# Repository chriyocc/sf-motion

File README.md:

# SF-Motion

**Open-source BLDC/PMSM motor control platform based on STM32 and Field-Oriented Control (FOC).**

The project includes:

- FOC firmware
- Custom motor driver hardware
- KiCad schematic and PCB design
- Gerber and BOM files
- Python communication and control tools
- PyQt/PyQtGraph GUI for motor monitoring and testing

> ⚠️ This project is under active development. Hardware and firmware may change between versions.

## My Tips
For everyday operation, calibration, control modes, plotting, and troubleshooting, see the [complete motor user guide](MOTOR_USER_GUIDE.md).

To start virtual env
`Set-ExecutionPolicy -Scope Process -ExecutionPolicy Bypass`
`.venv\Scripts\Activate.ps1`

To start GUI
`python communication/motor.py`

## Hardware Prerequisites

You will need:
- FOC Driver Board
- ST-Link programmer/debugger with 3-pin Molex pico-blade P1.25mm connector
- DC power supply
- BLDC/PMSM motor
- diametrical magnet
- USB type-C cable
- power cable with XT-30 female connector

The hardware design is available in:
```
Hardware/
├── production/        # Gerber manufacturing files
├── .kicad_sch         # Schematic
├── .kicad_pcb         # PCB design
└── ...
```

## Software Prerequisites

### 1. STM32CubeMX

Used to configure the STM32 peripherals and generate the initial project configuration.

Download: https://www.st.com/en/development-tools/stm32cubemx.html

### 2. Visual Studio Code

Used as the main development environment.

Download: https://code.visualstudio.com/

### 3. PlatformIO

PlatformIO is used to build and upload the firmware.

Install PlatformIO through the VS Code extension:
1. Open VS Code.
2. Open Extensions.
3. Search for PlatformIO IDE.
4. Install the extension.
5. Restart VS Code if required.

Verify the installation:
``` bash
pio --version
```

If `pio` is not recognized in the terminal, use the PlatformIO terminal inside VS Code or add the PlatformIO CLI directory to your system PATH.

### 4. Python

Python is required for the communication tools and GUI.

Recommended version:
```text
Python 3.10+
```

Download: https://www.python.org/downloads/

Check the installation:
``` bash
python --version
```

Create a virtual environment (recommended):
``` bash
python -m venv .venv
```

Activate it on Windows:
``` bash
.venv\Scripts\activate
```

Activate it on Linux/macOS:
``` bash
source .venv/bin/activate
```

Install the required packages:
``` bash
pip install numpy pyserial PyQt5 pyqtgraph keyboard
```

## Getting Started

Clone the repository using Git:
``` bash
git clone https://github.com/sirojudinMunir/sf-motion.git
```

Enter the project directory:
``` bash
cd SF-Motion
```

## Building the Firmware

Open the project in VS Code with PlatformIO installed.

Build the firmware:
``` bash
pio run
```

If the build is successful, the firmware binary will be generated by PlatformIO.

## Upload Firmware

Connect the ST-Link to the FOC Driver board using the 3-pin PicoBlade connector.

The board can be powered from a **6–24 V external power supply**. For the initial test, it is recommended to use **USB Type-C** as the power source if applicable.

Upload the firmware:
``` bash
pio run -t upload
```

You can also use the Upload button in the PlatformIO interface in VS Code.

## For the first test

After uploading the firmware, follow these steps:

1. Make sure the D3 LED is blinking after the firmware starts.
2. Connect the BLDC/PMSM motor wires to the FOC Driver board. Make sure the diametrical magnet is securely mounted on the motor shaft and properly aligned with the magnetic encoder on the FOC Driver board. The board should be positioned directly beneath the magnet.
3. If you are using an external power supply, set the current limit to 1 A for the initial test. This helps prevent damage if there is an unexpected issue with the board or motor.
4. Connect the USB Type-C cable to the board.
5. Run the Python motor control program:
    ```python
    python communication/motor.py
    ```
6. Select the correct COM port and click Connect.

7. Before running the motor, set the correct motor pole pairs:
    ``` python
    motor.set_pole_pairs(<your_motor_pole_pairs>)
    ```
    Replace <your_motor_pole_pairs> with the actual number of pole pairs of your motor.
8. Run the self-commissioning process:
    ``` python
    motor.self_commissioning()
    ```
    The self-commissioning process measures the motor resistance and inductance and calibrates the magnetic encoder.
    >Important: During encoder calibration, make sure the motor rotates counter-clockwise (CCW). If the motor rotates in the opposite direction, swap any two motor wires to reverse the rotation.
    Automatic motor direction detection will be implemented in a future version.
9. Save configuration
    ``` python
    motor.set_save_config()
    ```
10. Test the FOC motor modes using:
    ``` python
    motor.set_motor_mode(<mode>)
    ```
    Available modes:

    0 -> for current control mode  
    1 -> for speed control mode  
    2 -> for position control mode  
    5 -> for open-loop mode  
    6 -> for disable the motor

> ⚠️ Keep the power supply current limit low during the first test. Do not increase the voltage or current limit until the board, encoder, and motor are confirmed to be working correctly.

---

## Support SF-Motion

If you find this project useful and would like to support its development,
you can become a sponsor:

Your support helps fund hardware development, testing, documentation,
and future improvements to SF-Motion.

## Update Needed
- Implement overcurrent protection (send fault through CAN)
- 

## Updates compared with the earlier version (2026-09-23)

This section records the firmware, custom GUI, and communication fixes made after the PID/control review. The comparison is against the code before those fixes, rather than a tagged release.

### Firmware changes

| Area | Earlier behavior | Updated behavior |
| --- | --- | --- |
| Saved position PID cutoff | Startup replaced the saved derivative filter cutoff with 20 Hz. | Startup preserves the saved cutoff and recalculates its coefficient after setting the sampling period. |
| PI/PID anti-windup | The integral could keep growing when the proportional term, or combined P+D term, already exceeded the output limit. | Integration stops when it would drive the output further into saturation, while allowing the integral to unwind. |
| PID validation and acknowledgements | Negative gains could be ignored while returning success; negative output maxima could invert the bounds. | PID setters reject invalid values and return an error through the communication protocol. Validation includes non-finite values, ordered output bounds, nonnegative gains/deadbands, and positive filter cutoff and sampling period. |
| PID reset | Reset cleared the integral and previous error but retained filtered derivative history. | Reset also clears the filtered derivative history. |
| USB transmit buffer | A new frame could overwrite bytes still being used by an outstanding USB transfer. | CDC checks availability, then copies the frame into its own transmit buffer before starting the transfer. Oversized frames are rejected. |

### Custom GUI and Python communication changes

These control changes apply to `communication/plotter_custom.py`; the shared protocol changes are in `communication/SFMotionCom.py` and `communication/MotorProtocol.py`.

| Area | Earlier behavior | Updated behavior |
| --- | --- | --- |
| Disable command | A timeout while sending a zero current/speed setpoint could prevent the disable command from being sent. | The GUI attempts disable even when the preliminary zero fails. An unconfirmed disable is reported as unconfirmed. |
| Relative position moves | Targets used the last plotted angle, which became stale when plotting was paused. | The GUI reads the angle directly from the board before calculating a relative target. A failed or non-finite read cancels the move. The position demo also reads its starting angle directly. |
| Reconnect and Apply All | Previously loaded parameters remained eligible for Apply All after reconnecting. | Reconnect, disconnect, a failed Read All, or a failed Apply All invalidates the loaded-parameter state. A successful Read All is required before Apply All is allowed again. |
| PID input fields | PID fields allowed negative values regardless of their meaning. | Gains, deadbands, and output maxima are nonnegative; derivative cutoff is positive; field-weakening output minimum is nonpositive. The protocol validates all values in a PID group before its first write. |
| Request/reply handling | Requests consumed the next queued reply, allowing delayed replies to disrupt later requests. | Requests are serialized. A timeout, transport failure, or malformed/mismatched reply invalidates the session and requires reconnecting. A disable write remains possible, but is explicitly unconfirmed in that state. |
| Partial parameter updates | Failure during a group write could leave some registers updated without a clear recovery instruction. | Failures explicitly report a possible partial update and instruct the user to reconnect if required, then read parameters before retrying. |
| Connection setup failures | Only serial-specific exceptions were caught during connection setup. | Setup failures also clean up the connection and report the error. |

### Applying the update

- **Firmware changes require a successful flash and verification.** Building alone does not update the board.
- Build the main firmware with `pio run -e genericSTM32F405RG`. The output is `.pio/build/genericSTM32F405RG/firmware.bin`.
- **GUI changes require restarting the Python GUI.** After connecting, use Read All Parameters before Apply All.
- PID register mappings and the on-wire frame format remain unchanged.

### Validation and remaining limitations

- The main firmware build passed.
- All 16 Python GUI/protocol tests passed, including the two existing plotting tests and 14 new regression tests. Serial interactions in these tests are mocked.
- Added C regression tests for PI/PID saturation and unwinding, invalid values, filter initialization, and reset behavior. They were compiled with the ARM toolchain but have not been executed here.
- PID groups still use separate register writes; they are **not atomic**. A connection failure can leave a partial update, and automatic rollback is not attempted.
- Motor behavior and USB transfer behavior have not been verified on hardware. The reported CubeProgrammer erase failure remains unresolved; the updated firmware has not been confirmed installed on the board.
- The VCAP capacitor values discussed during troubleshooting are a hardware check, not a hardware modification included in this update.

See [hardware-free test instructions and communication recovery](tests/README.md) for details.

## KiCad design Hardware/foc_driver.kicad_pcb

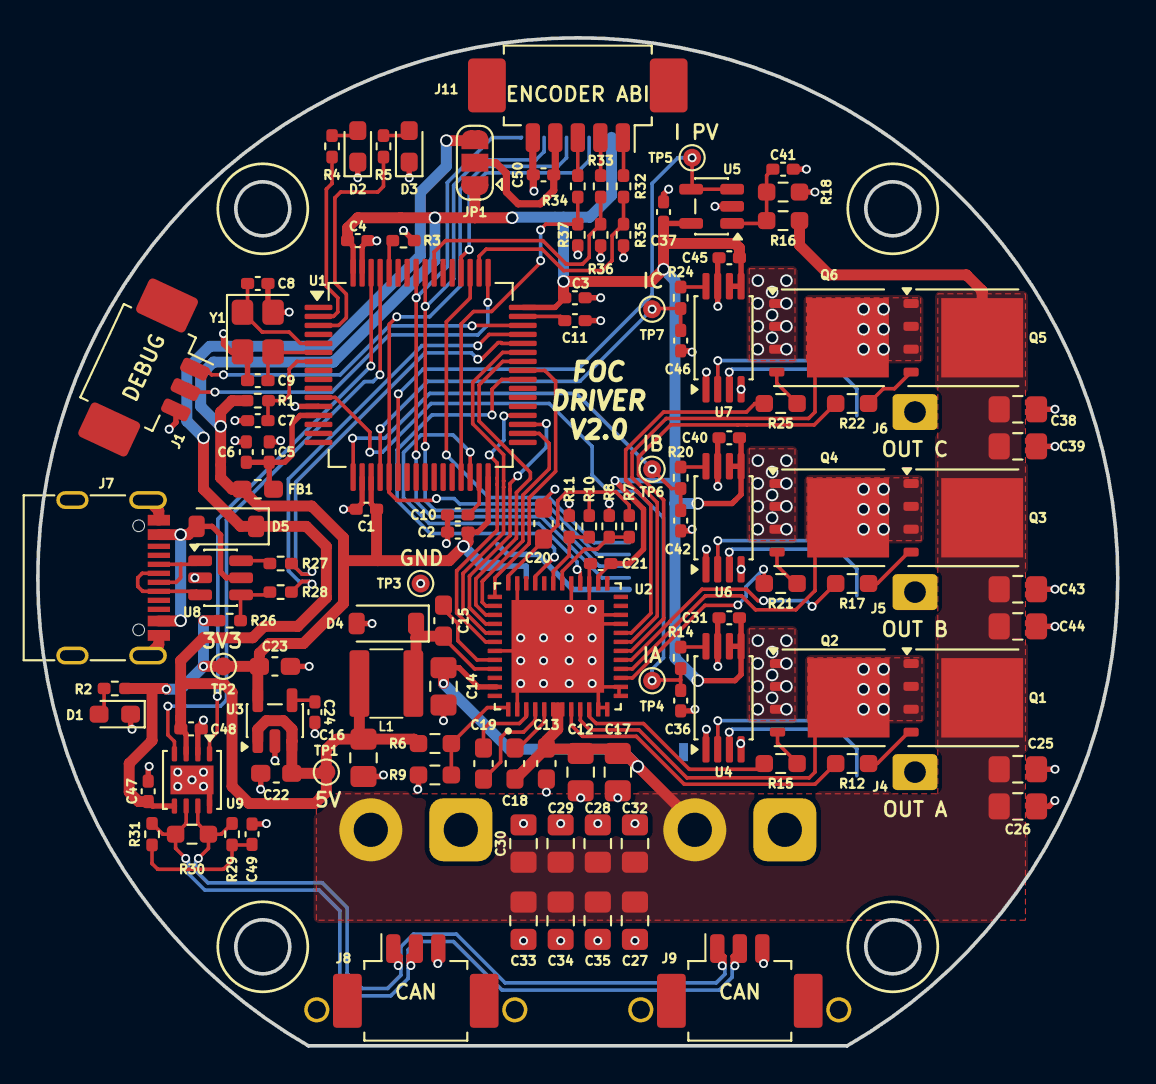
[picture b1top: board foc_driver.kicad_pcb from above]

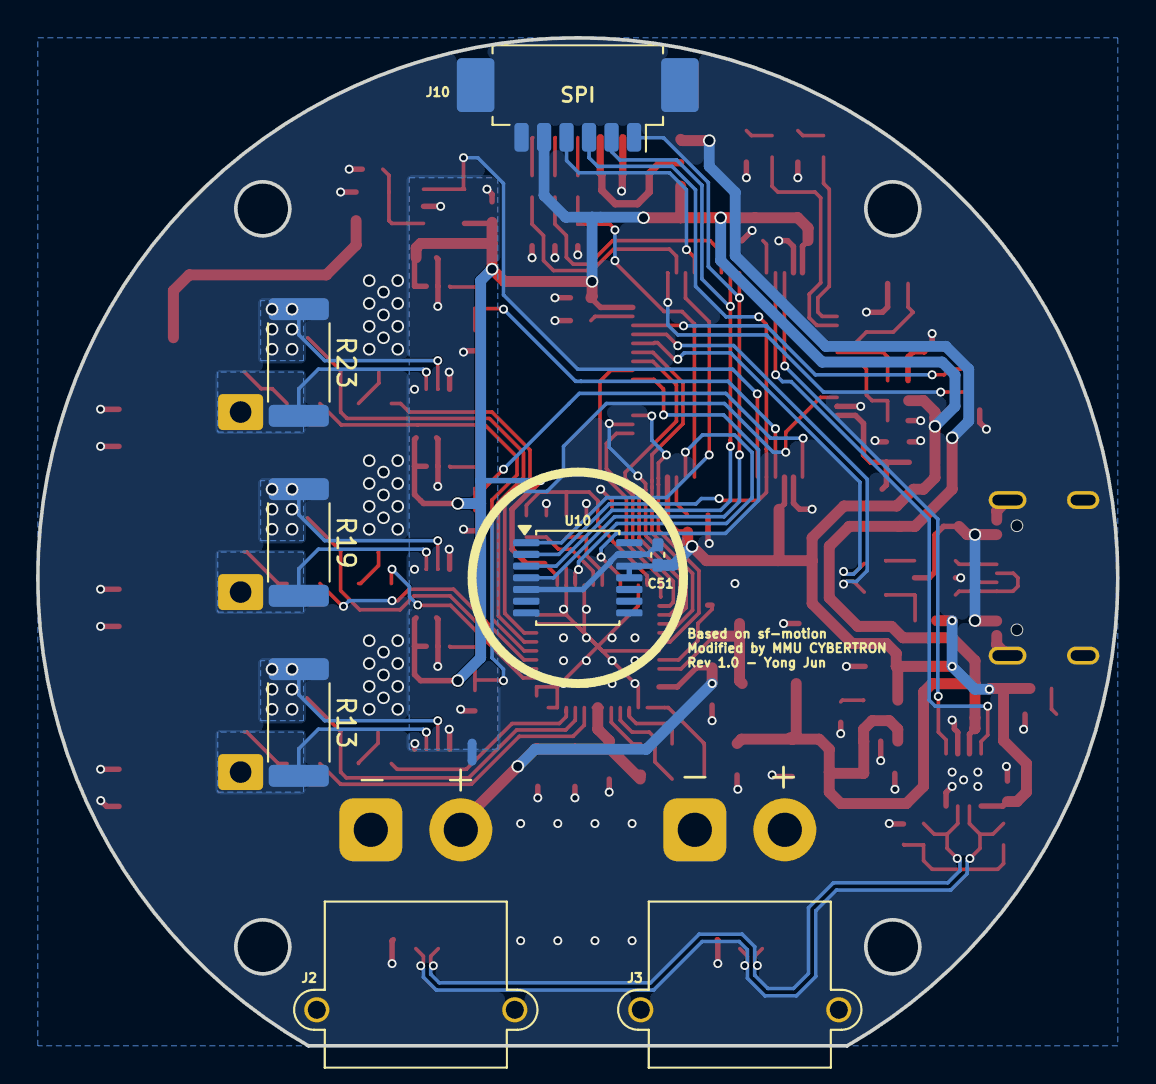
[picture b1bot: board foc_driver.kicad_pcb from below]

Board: 2 copper layers, 60.0 x 56.0 mm, 132 parts (9 on the bottom side), 87 nets.

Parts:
C1, C2, C3, C4, C5, C7, C10, C11, C21, C31, C37, C40, C41, C45, C47, C48, C49, C50, C51: 100nF; C_0402_1005Metric_Pad0.74x0.62mm_HandSolder
C6: 1uF; C_0402_1005Metric_Pad0.74x0.62mm_HandSolder
C8, C9: 33pF; C_0402_1005Metric_Pad0.74x0.62mm_HandSolder
C12, C16, C17, C25, C26, C27, C28, C29, C30, C32, C33, C34, C35, C38, C39, C43, C44: 10uF; C_0805_2012Metric_Pad1.18x1.45mm_HandSolder
C13, C15: 0.1uF; C_0603_1608Metric_Pad1.08x0.95mm_HandSolder
C14: 4.7uF; C_0805_2012Metric_Pad1.18x1.45mm_HandSolder
C18, C20, C22: 1uF; C_0603_1608Metric_Pad1.08x0.95mm_HandSolder
C19: 47nF; C_0603_1608Metric_Pad1.08x0.95mm_HandSolder
C23: 2.2uF; C_0603_1608Metric_Pad1.08x0.95mm_HandSolder
C24: 10nF; C_0402_1005Metric_Pad0.74x0.62mm_HandSolder
C36, C42, C46: 1nF; C_0402_1005Metric_Pad0.74x0.62mm_HandSolder
D1, D2: LED RED; LED_0603_1608Metric_Pad1.05x0.95mm_HandSolder
D3: LED GREEN; LED_0603_1608Metric_Pad1.05x0.95mm_HandSolder
D4, D5: MBR0530; D_SOD-123
FB1: fcm 1608-0603; L_0603_1608Metric_Pad1.05x0.95mm_HandSolder
J1, J8, J9: Conn_01x03_MountingPin; Molex_PicoBlade_53261-0371_1x03-1MP_P1.25mm_Horizontal
J2, J3: Conn_01x02; AMASS_XT30PW-M_1x02_P2.50mm_Horizontal
J4, J5, J6: Conn_01x01; SolderWire-0.25sqmm_1x01_D0.65mm_OD2mm
J7: USB_C_Receptacle_USB2.0_16P; USB_C_Receptacle_G-Switch_GT-USB-7010ASV
J10: Conn_01x06_MountingPin; Molex_PicoBlade_53261-0671_1x06-1MP_P1.25mm_Horizontal
J11: Conn_01x05_MountingPin; Molex_PicoBlade_53261-0571_1x05-1MP_P1.25mm_Horizontal
JP1: SolderJumper_3_Open; SolderJumper-3_P1.3mm_Open_RoundedPad1.0x1.5mm
L1: 22uH; L_SMD_4X4
NT1: NetTie_2; NetTie-2_SMD_Pad0.5mm
Q1, Q2, Q3, Q4, Q5, Q6: WSD30100DN56; TDSON-8-1
R1, R3: 10k; R_0402_1005Metric_Pad0.72x0.64mm_HandSolder
R2, R4, R5, R14, R20, R24, R32, R33, R34: 1k; R_0402_1005Metric_Pad0.72x0.64mm_HandSolder
R6: 18k; R_0603_1608Metric_Pad0.98x0.95mm_HandSolder
R7, R8, R10, R11: R; R_0402_1005Metric_Pad0.72x0.64mm_HandSolder
R9: 3k3; R_0603_1608Metric_Pad0.98x0.95mm_HandSolder
R12, R15, R17, R21, R22, R25: 10R; R_0603_1608Metric_Pad0.98x0.95mm_HandSolder
R13, R19, R23: 0.01R; R_2512_6332Metric
R16: 39k; R_0603_1608Metric_Pad0.98x0.95mm_HandSolder
R18: 2k2; R_0603_1608Metric_Pad0.98x0.95mm_HandSolder
R26: 1k8; R_0402_1005Metric_Pad0.72x0.64mm_HandSolder
R27, R28: 100R; R_0402_1005Metric_Pad0.72x0.64mm_HandSolder
R29, R31: 30R; R_0402_1005Metric_Pad0.72x0.64mm_HandSolder
R30: 120R; R_0603_1608Metric_Pad0.98x0.95mm_HandSolder
R35, R36, R37: 2k; R_0402_1005Metric_Pad0.72x0.64mm_HandSolder
TP1, TP2, TP3, TP4, TP5, TP6, TP7: TestPoint; TestPoint_Pad_D1.0mm
U1: STM32F405RGTx; LQFP-64_10x10mm_P0.5mm
U2: DRV8323RHRGZR; QFN50P700X700X100-49N
U3: LP2985-3.3; SOT-23-5
U4, U6, U7: INA240A1PW; TSSOP-8_4.4x3mm_P0.65mm
U5: LM321; SOT-23-5
U8: USBLC6-2SC6; SOT-23-6
U9: TJA1051TK-3; HVSON-8-1EP_3x3mm_P0.65mm_EP1.6x2.4mm
U10: AS5047D; TSSOP-14_4.4x5mm_P0.65mm
Y1: 12MHz; Crystal_SMD_3225-4Pin_3.2x2.5mm

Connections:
+3V3: C1.1, C2.1, C3.1, C4.1, C21.2, C23.1, C31.1, C37.1, C40.1, C45.1, C47.2, C51.1, FB1.2, J10.5, JP1.1 (A), R1.1, R2.1, R26.1, TP2.1 (1_1), U1.19 (VDD), U1.32 (VDD), U1.48 (VDD), U1.64 (VDD), U2.26 (VREF), U3.5 (VOUT), U4.5 (V+), U4.6 (REF2), U5.5 (V+), U6.5 (V+), U6.6 (REF2), U7.5 (V+), U7.6 (REF2), U9.5 (VIO), U10.11 (VDD), U10.12 (VDD3V3)
+3V3A: C5.1, C6.1, FB1.1, U1.13 (VDDA)
+5V: C16.1, C22.1, C48.2, D5.1 (K), JP1.3 (B), L1.2, R6.1, TP1.1 (1_1), U3.1 (VIN), U3.3 (ON/~OFF), U9.3 (VCC)
/Communications/CAN_N: J8.2, J9.2, R30.2, R31.2, U9.6 (CANL)
/Communications/CAN_P: J8.1, J9.1, R29.2, R30.1, U9.7 (CANH)
/Communications/CAN_RX: U1.61 (PB8), U9.4 (RXD)
/Communications/CAN_TX: U1.62 (PB9), U9.1 (TXD)
/Communications/USB_N: R27.2, U1.44 (PA11)
/Communications/USB_P: R28.2, U1.45 (PA12)
/Communications/VBUS: D5.2 (A), J7.A4 (VBUS), J7.A9 (VBUS), J7.B4 (VBUS), J7.B9 (VBUS), U8.5 (VBUS)
/Encoders/CS0: U1.51 (PC10), U10.1 (~CS)
/Encoders/CS1: J10.4, U1.52 (PC11)
/Encoders/EXT_ENCDA: R32.1, R35.1, U1.50 (PA15)
/Encoders/EXT_ENCDB: R33.1, R36.1, U1.55 (PB3)
/Encoders/EXT_ENCDI: R34.1, R37.1, U1.29 (PB10)
/Encoders/MISO: J10.2, U1.56 (PB4), U10.3 (MISO)
/Encoders/MOSI: J10.1, U1.57 (PB5), U10.4 (MOSI)
/Encoders/SCK: J10.3, U1.21 (PA5), U10.2 (CLK)
/Gate Driver/EN_GATE: U1.40 (PC9), U2.33 (ENABLE)
/Gate Driver/FAULT: U1.30 (PB11), U2.28 (NFAULT)
/Gate Driver/GHA: R12.1, U2.8 (GHA)
/Gate Driver/GHB: R17.1, U2.17 (GHB)
/Gate Driver/GHC: R22.1, U2.18 (GHC)
/Gate Driver/GLA: R15.1, U2.10 (GLA)
/Gate Driver/GLB: R21.1, U2.15 (GLB)
/Gate Driver/GLC: R25.1, U2.20 (GLC)
/Gate Driver/IDRIVE: R7.2, R8.2, U2.30 (IDRIVE)
/Gate Driver/INH_A: U1.41 (PA8), U2.37 (INHA)
/Gate Driver/INH_B: U1.42 (PA9), U2.39 (INHB)
/Gate Driver/INH_C: U1.43 (PA10), U2.41 (INHC)
/Gate Driver/INL_A: U1.34 (PB13), U2.38 (INLA)
/Gate Driver/INL_B: U1.35 (PB14), U2.40 (INLB)
/Gate Driver/INL_C: U1.36 (PB15), U2.42 (INLC)
/Gate Driver/SHA: Q1.1 (S), Q1.2 (S), Q1.3 (S), Q2.5 (D), R13.1, U2.9 (SHA), U4.2 (+)
/Gate Driver/SHB: Q3.1 (S), Q3.2 (S), Q3.3 (S), Q4.5 (D), R19.1, U2.16 (SHB), U6.2 (+)
/Gate Driver/SHC: Q5.1 (S), Q5.2 (S), Q5.3 (S), Q6.5 (D), R23.1, U2.19 (SHC), U7.2 (+)
/Gate Driver/VDS: R10.2, R11.2, U2.31 (VDS)
/Inverter/ISENSE_A: C36.1, R14.2, TP4.1 (1_1), U1.11 (PC3)
/Inverter/ISENSE_B: C42.1, R20.2, TP6.1 (1_1), U1.17 (PA3)
/Inverter/ISENSE_C: C46.1, R24.2, TP7.1 (1_1), U1.20 (PA4)
/Inverter/OUT_A: J4.1 (Pin_1_1), R13.2, U4.3 (-)
/Inverter/OUT_B: J5.1 (Pin_1_1), R19.2, U6.3 (-)
/Inverter/OUT_C: J6.1 (Pin_1_1), R23.2, U7.3 (-)
/Inverter/PV_SENSE: TP5.1 (1_1), U1.22 (PA6), U5.3 (-), U5.4
/MCU/BOOT0: R3.2, U1.60 (BOOT0)
/MCU/LED_G: R5.1, U1.3 (PC14)
/MCU/LED_R: R4.1, U1.2 (PC13)
/MCU/NRST: C7.1, R1.2, U1.7 (NRST)
/MCU/OSC_IN: C8.2, U1.5 (PH0), Y1.1
/MCU/OSC_OUT: C9.2, U1.6 (PH1), Y1.3
/MCU/SWCLK: J1.2, U1.49 (PA14)
/MCU/SWDIO: J1.1, U1.46 (PA13)
DVDD: C20.1, R7.1, R10.1, U2.36 (DVDD)
GND: C1.2, C2.2, C3.2, C4.2, C5.2, C6.2, C7.2, C8.1, C9.1, C10.2, C11.2, C12.2, C13.2, C14.2, C16.2, C17.2, C20.2, C21.1, C22.2, C23.2, C24.2, C25.1, C26.1, C27.1, C28.1, C29.1, C30.1, C32.1, C33.1, C34.1, C35.1, C38.1, C39.1, C41.2, C43.1, C44.1, C47.1, C48.1, C49.1, C50.1, C51.2, D1.1 (K), D2.1 (K), D3.1 (K), D4.2 (A), J1.3, J2.1, J3.1, J7.A1 (GND), J7.A12 (GND), J7.B1 (GND), J7.B12 (GND), J7.S1 (SHIELD), J8.3, J9.3, J10.6, J11.5, NT1.2, Q2.1 (S), Q2.2 (S), Q2.3 (S), Q4.1 (S), Q4.2 (S), Q4.3 (S), Q6.1 (S), Q6.2 (S), Q6.3 (S), R3.1, R8.1, R9.2, R11.1, R18.2, R35.2, R36.2, R37.2, TP3.1 (1_1), U1.12 (VSSA), U1.18 (VSS), U1.63 (VSS), U2.2 (PGND), U2.11 (SPA), U2.12 (SNA), U2.13 (SNB), U2.14 (SPB), U2.21 (SPC), U2.22 (SNC), U2.27 (DGND), U2.29 (MODE), U2.35 (AGND), U2.43 (BGND), U2.49 (EP), U3.2 (GND), U8.2 (GND), U9.2 (GND), U9.8 (S), U9.9 (GND), U10.5 (TST), U10.13 (GND), Y1.2 (G), Y1.4 (G)
GNDA: C31.2, C36.2, C37.2, C40.2, C42.2, C45.2, C46.2, NT1.1, U4.1 (GND), U4.4 (GND), U4.7 (REF1), U5.2 (V-), U6.1 (GND), U6.4 (GND), U6.7 (REF1), U7.1 (GND), U7.4 (GND), U7.7 (REF1)
unnamed: C49.2, R29.1, R31.1
unnamed: D1.2 (A), R2.2
unnamed: D2.2 (A), R4.2
unnamed: D3.2 (A), R5.2
unnamed: C15.2, D4.1 (K), L1.1, U2.45 (SW)
unnamed: J7.A6 (D+), J7.B6 (D+), U8.3 (I/O2)
unnamed: J7.A7 (D-), J7.B7 (D-), U8.1 (I/O1)
unnamed: J11.1, R32.2
unnamed: J11.2, R33.2
unnamed: J11.3, R34.2
unnamed: C50.2, J11.4, JP1.2 (C)
unnamed: Q1.4 (G), R12.2
unnamed: Q2.4 (G), R15.2
unnamed: Q3.4 (G), R17.2
unnamed: Q4.4 (G), R21.2
unnamed: Q5.4 (G), R22.2
unnamed: Q6.4 (G), R25.2
unnamed: R14.1, U4.8
unnamed: R20.1, U6.8
unnamed: R24.1, U7.8
unnamed: R26.2, R28.1, U8.4 (I/O2)
unnamed: R27.1, U8.6 (I/O1)
unnamed: C10.1, U1.31 (VCAP_1)
unnamed: C11.1, U1.47 (VCAP_2)
unnamed: C15.1, U2.44 (CB)
unnamed: C19.2, U2.4 (CPH)
unnamed: C19.1, U2.3 (CPL)
unnamed: R6.2, R9.1, U2.1 (FB)
unnamed: C18.1, U2.5 (VCP)
unnamed: C24.1, U3.4 (BP)
unnamed: C41.1, R16.2, R18.1, U5.1 (+)
VS: C12.1, C13.1, C14.1, C17.1, C18.2, C25.2, C26.2, C27.2, C28.2, C29.2, C30.2, C32.2, C33.2, C34.2, C35.2, C38.2, C39.2, C43.2, C44.2, J2.2, J3.2, Q1.5 (D), Q3.5 (D), Q5.5 (D), R16.1, U2.6 (VM), U2.7 (VDRAIN), U2.47 (VIN)

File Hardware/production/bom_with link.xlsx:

Designator | Footprint | Quantity | Value | LCSC Part # |  | Link
C1, C10, C11, C2, C21, C3, C31, C37, C4, C40, C41, C45, C47, C48, C49, C5, C50,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 | 0402 | 19 | 100nF | C1525 |  | https://item.taobao.com/item.htm?id=619644090710&mi_id=0000o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
C12, C16, C17, C25, C26, C27, C28, C29, C30, C32, C33, C34, C35, C38, C39, C43,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 | 0805 | 17 | 10uF | C22367830 |  | https://item.taobao.com/item.htm?id=537776958252&mi_id=0000S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
C13, C15 | 0603 | 2 | 0.1uF | C1591 |  | https://item.taobao.com/item.htm?id=537669338432&mi_id=0000b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
C14 | 0805 | 1 | 4.7uF | C98192 |  | https://item.taobao.com/item.htm?id=522572786930&mi_id=0000b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
C18, C20, C22 | 0603 | 3 | 1uF | C5199872 |  | https://item.taobao.com/item.htm?id=537669338432&mi_id=0000b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
C19 | 0603 | 1 | 47nF | C1622 |  | https://item.taobao.com/item.htm?id=537669338432&mi_id=0000b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
C23 | 0603 | 1 | 2.2uF | C23630 |  | https://item.taobao.com/item.htm?id=537669338432&mi_id=0000b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
C24 | 0402 | 1 | 10nF | C15195 |  | https://item.taobao.com/item.htm?id=523808399191&mi_id=0000r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
C36, C42, C46 | 0402 | 3 | 1nF | C14442 |  | https://item.taobao.com/item.htm?id=523808399191&mi_id=0000r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
C6 | 0402 | 1 | 1uF | C29266 |  | https://item.taobao.com/item.htm?id=523832610965&mi_id=0000I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
C8, C9 | 0402 | 2 | 33pF | C70465 |  | https://item.taobao.com/item.htm?id=574673920044&mi_id=0000d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
D1, D2 | 0603 | 2 | LED RED | C19171390 |  | https://item.taobao.com/item.htm?id=607210300413&mi_id=00001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
D3 | 0603 | 1 | LED GREEN | C2986048 |  | https://item.taobao.com/item.htm?id=522573309525&mi_id=00008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
D4, D5 | D_SOD-123 | 2 | MBR0530 | C5204746 |  | https://item.taobao.com/item.htm?id=685355899371&mi_id=0000v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
FB1 | 0603 | 1 | fcm 1608-0603 | C19330 |  | https://item.taobao.com/item.htm?id=522576784852&mi_id=0000g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
J1, J8, J9 | Molex_PicoBlade_53261-0371_1x03-1MP_P1.25mm_Horizontal | 3 | Conn_01x03_MountingPin | C293630 |  | https://item.taobao.com/item.htm?id=528734911747&mi_id=0000o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
J10 | Molex_PicoBlade_53261-0671_1x06-1MP_P1.25mm_Horizontal | 1 | Conn_01x06_MountingPin | C17393620 |  | https://item.taobao.com/item.htm?id=528734911747&mi_id=0000o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
J11 | Molex_PicoBlade_53261-0571_1x05-1MP_P1.25mm_Horizontal | 1 | Conn_01x05_MountingPin | C17256390 |  | https://item.taobao.com/item.htm?id=528734911747&mi_id=0000o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
J2, J3 | AMASS_XT30PW-M_1x02_P2.50mm_Horizontal | 2 | Conn_01x02 | C431092 |  | https://item.taobao.com/item.htm?id=635227665423&mi_id=00001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
J4, J5, J6 | SolderWire-0.25sqmm_1x01_D0.65mm_OD2mm | 3 | Conn_01x01
J7 | USB_C_Receptacle_G-Switch_GT-USB-7010ASV | 1 | USB_C_Receptacle_USB2.0_16P | C2927039 |  | https://item.taobao.com/item.htm?id=573090887123&mi_id=0000A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
L1 | L_SMD_4X4 | 1 | 22uH | C6364792 |  | https://item.taobao.com/item.htm?id=589062675723&mi_id=0000r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
Q1, Q2, Q3, Q4, Q5, Q6 | TDSON-8-1 | 6 | WSD30100DN56 | C2862136 |  | https://item.taobao.com/item.htm?id=663046959853&mi_id=0000y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
R1, R3 | 0402 | 2 | 10k | C60490 |  | https://item.taobao.com/item.htm?id=523791322923&mi_id=0000C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
R10, R11, R7, R8 | 0402 | 4 | R | Use 75k for R8,R11 |  | https://item.taobao.com/item.htm?id=525634101247&mi_id=0000g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
R12, R15, R17, R21, R22, R25 | 0603 | 6 | 10R | C844919 |  | https://item.taobao.com/item.htm?id=525741229141&mi_id=0000l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
R13, R19, R23 | R_Shunt_Ohmite_LVK20 | 3 | 0.01R | C844898
R14, R2, R20, R24, R32, R33, R34, R4, R5 | 0402 | 9 | 1k | C852624 |  | https://item.taobao.com/item.htm?id=559832085134&mi_id=0000U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
R16 | 0603 | 1 | 39k | C163424 |  | https://item.taobao.com/item.htm?id=525898564027&mi_id=0000P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
R18 | 0603 | 1 | 2k2 | C125931 |  | https://item.taobao.com/item.htm?id=525826728150&mi_id=0000_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
R26 | 0402 | 1 | 1k8 | C163481 |  | https://item.taobao.com/item.htm?id=632063701563&mi_id=0000A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
R27, R28 | 0402 | 2 | 100R | C705627 |  | https://item.taobao.com/item.htm?id=559832085134&mi_id=0000U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
R29, R31 | 0402 | 2 | 30R | C852718 |  | https://item.taobao.com/item.htm?id=631379668328&mi_id=0000O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
R30 | 0603 | 1 | 120R | C125925 |  | https://item.taobao.com/item.htm?id=525596814299&mi_id=0000y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
R35, R36, R37 | 0402 | 3 | 2k | C852711 |  | https://item.taobao.com/item.htm?id=631736632107&mi_id=0000a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
R6 | 0603 | 1 | 18k | C309650 |  | https://item.taobao.com/item.htm?id=559889370450&mi_id=0000x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
R9 | 0603 | 1 | 3k3 | C144661 |  | https://item.taobao.com/item.htm?id=525777943950&mi_id=0000Z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
TP1, TP2, TP3, TP4, TP5, TP6, TP7 | TestPoint_Pad_D1.0mm | 7 | TestPoint
U1 | LQFP-64_10x10mm_P0.5mm | 1 | STM32F405RGTx | C15742 |  | https://item.taobao.com/item.htm?id=522577756409&mi_id=0000X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
U10 | TSSOP-14_4.4x5mm_P0.65mm | 1 | AS5047D | C2693743 |  | https://item.taobao.com/item.htm?id=1029683823182&mi_id=0000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
U2 | QFN50P700X700X100-49N | 1 | DRV8323RHRGZR | C543035 |  | https://item.taobao.com/item.htm?spm=a1z0d.6639537%2F202410.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
U3 | SOT-23-5 | 1 | LP2985-3.3 | C95414 |  | https://item.taobao.com/item.htm?id=572237742889&mi_id=0000L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
U4, U6, U7 | TSSOP-8_4.4x3mm_P0.65mm | 3 | INA240A1PW | C93965 |  | https://item.taobao.com/item.htm?id=756730260979&mi_id=0000E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
U5 | SOT-23-5 | 1 | LM321 | C5252901 |  | https://item.taobao.com/item.htm?id=666849623425&mi_id=0000k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
U8 | SOT-23-6 | 1 | USBLC6-2SC6 | C2827654 |  | https://item.taobao.com/item.htm?id=763430084934&mi_id=0000e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
U9 | HVSON-8-1EP_3x3mm_P0.65mm_EP1.6x2.4mm | 1 | TJA1051TK-3 | C2875699 |  | https://item.taobao.com/item.htm?id=736463710815&mi_id=0000J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
Y1 | Crystal_SMD_3225-4Pin_3.2x2.5mm | 1 | 12MHz | C9002 |  | https://item.taobao.com/item.htm?id=534883366755&mi_id=0000z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
